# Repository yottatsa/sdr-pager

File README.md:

# Motorola Advisor-style radio-on-chip receiver board

## SI4432
Other implementations of the driver:

* https://github.com/peterantypas/maiana
* https://github.com/astuder/dAISy
* https://github.com/eugmes/ais-recv-fw
* https://github.com/kgoba/si4060test

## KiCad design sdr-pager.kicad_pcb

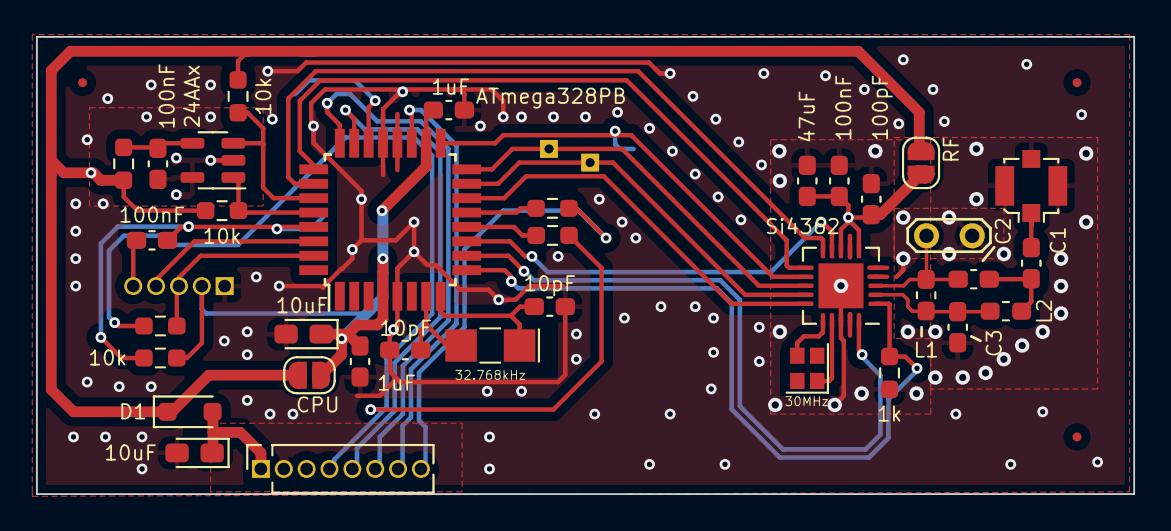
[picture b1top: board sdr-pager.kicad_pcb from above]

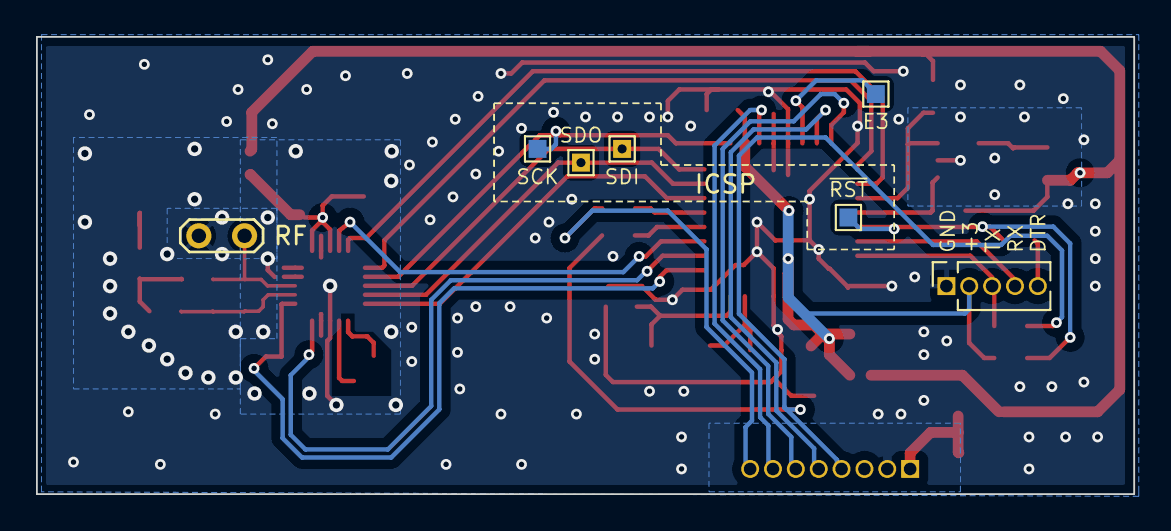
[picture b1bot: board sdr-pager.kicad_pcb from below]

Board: 2 copper layers, 61.0 x 25.4 mm, 44 parts (7 on the bottom side), 37 nets.

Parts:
C1: C1; C_0603_1608Metric_Pad1.08x0.95mm_HandSolder
C2: C2; C_0603_1608Metric_Pad1.08x0.95mm_HandSolder
C3: C3; C_0603_1608Metric_Pad1.08x0.95mm_HandSolder
C4: 100pF; C_0603_1608Metric_Pad1.08x0.95mm_HandSolder
C5, C11, C12: 100nF; C_0603_1608Metric_Pad1.08x0.95mm_HandSolder
C6: 47uF; C_0603_1608Metric_Pad1.08x0.95mm_HandSolder
C7, C8: 1uF; C_0603_1608Metric_Pad1.08x0.95mm_HandSolder
C9, C10: 10pF; C_0603_1608Metric_Pad1.08x0.95mm_HandSolder
CP1, CP2: 10uF; CP_EIA-2012-12_Kemet-R_Pad1.30x1.05mm_HandSolder
D1: VCC; D_SOD-323_HandSoldering
FID1, FID2, FID3: Fiducial; Fiducial_0.5mm_Mask1.5mm
J1: Motorola Pager RF; PinSocket_1x08_P1.27mm_Vertical
J2: UART; PinSocket_1x05_P1.27mm_Vertical
J3: RF; U.FL_Molex_MCRF_73412-0110_Vertical
JP1: RF; SolderJumper-2_P1.3mm_Open_RoundedPad1.0x1.5mm
JP2: CPU; SolderJumper-2_P1.3mm_Open_RoundedPad1.0x1.5mm
L1: L1; L_0603_1608Metric_Pad1.05x0.95mm_HandSolder
L2: L2; L_0603_1608Metric_Pad1.05x0.95mm_HandSolder
R1, R4, R5: 10k; R_0603_1608Metric_Pad0.98x0.95mm_HandSolder
R2: 1k; R_0603_1608Metric_Pad0.98x0.95mm_HandSolder
R3, R6, R7, R9: 0; R_0603_1608Metric_Pad0.98x0.95mm_HandSolder
TP1: RF; TestPoint_2Pads_Pitch2.54mm_Drill0.8mm
TP2: E3; TestPoint_Pad_1.0x1.0mm
TP3: SDO; TestPoint_THTPad_1.0x1.0mm_Drill0.5mm
TP4: SDI; TestPoint_THTPad_1.0x1.0mm_Drill0.5mm
TP8: SCK; TestPoint_Pad_1.0x1.0mm
TP9: ~{RST}; TestPoint_Pad_1.0x1.0mm
U1: ATmega328PB; TQFP-32_7x7mm_P0.8mm
U2: Si4362; QFN-20-1EP_4x4mm_P0.5mm_EP2.5x2.5mm
U3: 24AAx; SOT-23-5
Y1: 30MHz; Crystal_SMD_2016-4Pin_2.0x1.6mm
Y2: 32.768kHz; Crystal_SMD_EuroQuartz_EQ161-2Pin_3.2x1.5mm_HandSoldering

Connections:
/E.SDO: TP2.1, U1.22 (PE3)
AUDIO: J1.8, R7.1
B++: CP1.1, D1.2 (A), J1.1
CPU.VDD: C7.1, C8.1, CP2.1, J2.2, JP2.1 (A), R1.1, U1.4 (VCC), U1.18 (AVCC)
CPU.XIN: C9.1, U1.7 (XTAL1/PB6), Y2.2
CPU.XOUT: C10.1, U1.8 (XTAL2/PB7), Y2.1
DTR: C11.2, J2.5
E.SCK: J1.6, U1.24 (PC1)
E.SDI: J1.5, U1.23 (PC0)
E.SS: J1.7, U1.19 (PE2)
GND: C3.1, C4.2, C5.2, C6.2, C7.2, C8.2, C9.2, C10.2, C12.2, CP1.2, CP2.2, J1.2, J2.1, J3.2 (Ext), R2.1, TP1.2, U1.5 (GND), U1.21 (GND), U2.18 (GND), U2.21 (GND), U3.2 (V_{SS}), U3.5 (WP)
I2C1.SCL: R5.2, U1.28 (PC5), U3.1 (SCL)
I2C1.SDA: R4.1, U1.27 (PC4), U3.3 (SDA)
I.IRQ: U1.25 (PC2), U2.11 (~IRQ)
I.SCK: TP8.1, U1.17 (PB5), U2.12 (SCLK)
I.SDI: TP3.1, U1.15 (PB3), U2.14 (SDI)
I.SDO: TP4.1, U1.16 (PB4), U2.13 (SDO)
I.~SS: U1.14 (PB2), U2.15 (~SEL)
LIM_DATA: J1.4, R6.1, R9.1
unnamed: C1.1, J3.1 (In)
unnamed: C1.2, C2.1, L2.1
unnamed: R9.2, U1.12 (PB0)
unnamed: R7.2, U1.13 (PB1)
unnamed: C12.1, R3.1, U3.4 (V_{CC})
RF.A+: C3.2, L1.2, L2.2, U2.2 (RXp)
RF.A-: C2.2, L1.1, TP1.1, U2.3 (RXn)
RF.DOWN: R2.2, U1.9 (PD5), U2.1 (SDN)
RF.GPIO0: U1.11 (PD7), U2.9 (GPIO0)
RF.GPIO1: U1.26 (PC3), U2.10 (GPIO1)
RF.GPIO3: U1.10 (PD6), U2.20 (GPIO3)
RF.VDD: C4.1, C5.1, C6.1, JP1.1 (A), U2.6 (VDD), U2.8 (VDD)
RF.XIN: U2.17 (XIN), Y1.1
RF.XOUT: U2.16 (XOUT), Y1.3
UART1.IN: J2.4, U1.30 (PD0)
UART1.OUT: J2.3, R6.2, U1.31 (PD1)
VDD: D1.1 (K), JP1.2 (B), JP2.2 (B), R3.2, R4.2, R5.1
~RESET: C11.1, R1.2, TP9.1, U1.29 (~RESET/PC6)

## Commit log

2024-05-17 initial
2024-06-04 skeleton to talk to radio
2024-06-04 icsp, registers
2024-06-04 properties, standby
2024-06-13 freq calculation, setprop macro
2024-12-22 links
